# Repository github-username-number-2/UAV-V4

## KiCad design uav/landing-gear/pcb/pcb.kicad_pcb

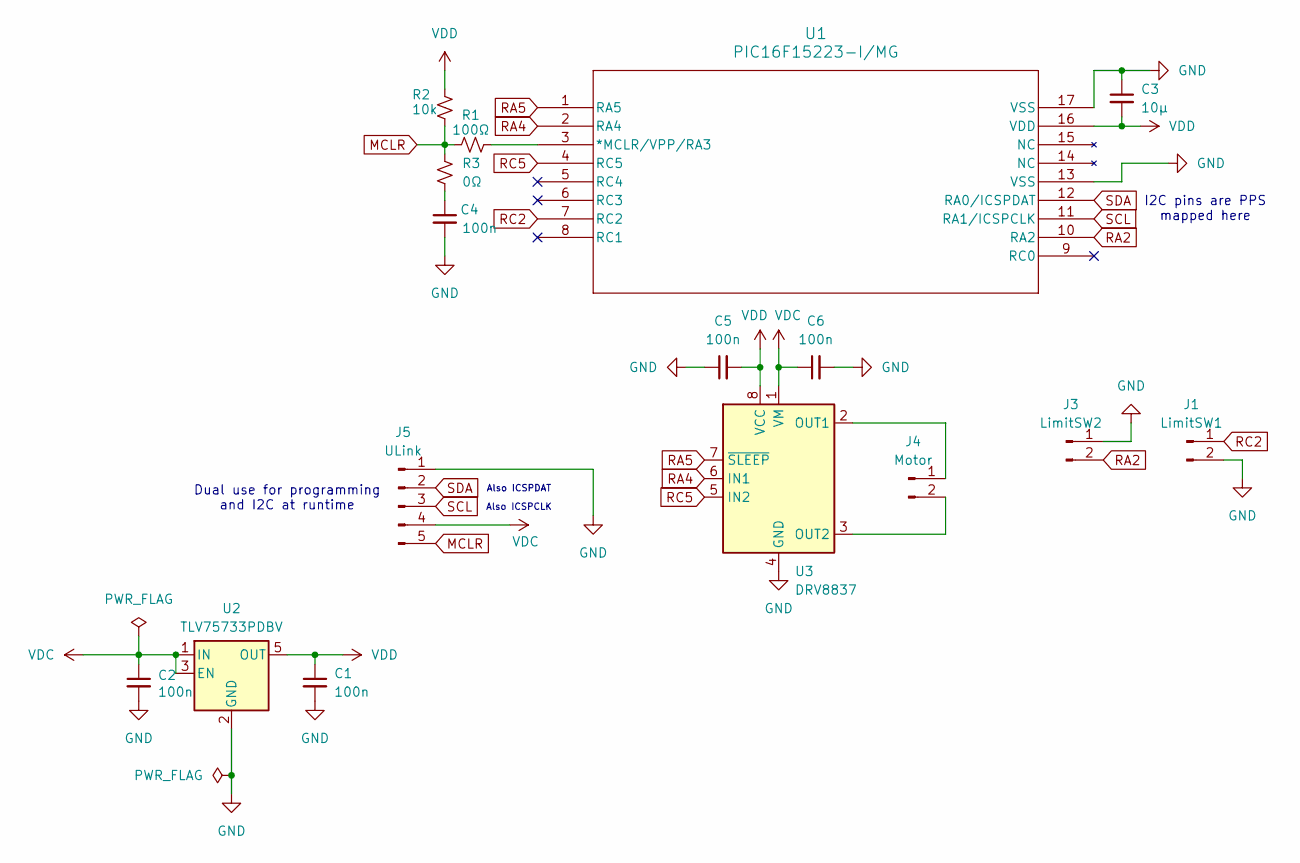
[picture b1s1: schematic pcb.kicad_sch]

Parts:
C1, C2, C4, C5, C6: 100n; C_0402_1005Metric
C3: 10µ; C_0805_2012Metric
J1: LimitSW1; JST_ZH_B2B-ZR_1x02_P1.50mm_Vertical
J3: LimitSW2; JST_ZH_B2B-ZR_1x02_P1.50mm_Vertical
J4: Motor; JST_ZH_B2B-ZR_1x02_P1.50mm_Vertical
J5: ULink; JST_PH_B5B-PH-K_1x05_P2.00mm_Vertical
R1: 100Ω; R_0402_1005Metric
R2: 10k; R_0402_1005Metric
R3: 0Ω; PinHeader_1x02_P1.27mm_Vertical
U1: PIC16F15223-I/MG; QFN16_MG_MCH
U2: TLV75733PDBV; SOT-23-5
U3: DRV8837; WSON-8-1EP_2x2mm_P0.5mm_EP0.9x1.6mm_ThermalVias

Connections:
GND: C1.2, C2.2, C3.1, C4.2, C5.1, C6.2, J1.2, J3.1, J5.1, U1.13 (VSS), U1.17 (VSS), U2.2 (GND), U3.4 (GND), U3.9 (GND)
MCLR: J5.5, R1.1, R2.2, R3.1
unnamed: C4.1, R3.2
unnamed: J4.1, U3.2 (OUT1)
unnamed: J4.2, U3.3 (OUT2)
unnamed: R1.2, U1.3 (*MCLR/VPP/RA3)
RA2: J3.2, U1.10 (RA2)
RA4: U1.2 (RA4), U3.6 (IN1)
RA5: U1.1 (RA5), U3.7 (~SLEEP)
RC2: J1.1, U1.7 (RC2)
RC5: U1.4 (RC5), U3.5 (IN2)
SCL: J5.3, U1.11 (RA1/ICSPCLK)
SDA: J5.2, U1.12 (RA0/ICSPDAT)
VDC: C2.1, C6.1, J5.4, U2.1 (IN), U2.3 (EN), U3.1 (VM)
VDD: C1.1, C3.2, C5.2, R2.1, U1.16 (VDD), U2.5 (OUT), U3.8 (VCC)

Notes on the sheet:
Also ICSPCLK
Also ICSPDAT
Dual use for programming and I2C at runtime
I2C pins are PPS mapped here

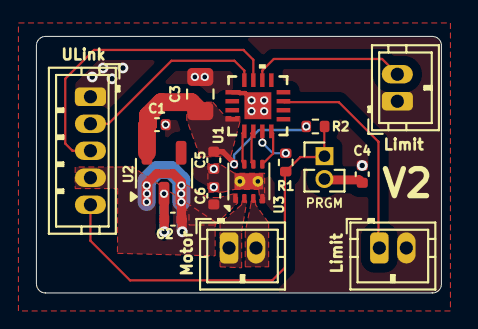
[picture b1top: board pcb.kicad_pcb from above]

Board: 2 copper layers, 22.5 x 14.2 mm, 16 parts (0 on the bottom side), 15 nets.

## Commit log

2025-03-04 finish landing gear pcb
2025-04-13 clean drc
